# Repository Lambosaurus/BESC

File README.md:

# BESC

## Control-HW
This component is the ESC control board - that is, everything except the FET's.

Firmware for this is the [simon-k](https://github.com/sim-/tgy) `rb70a.hex`.

Based on this, the pinout will be:

| Signal         | Simon-k | Pin | 
| -------------- | ------- | --- |
| PWM_AL         | AnFET   | PD0 | 
| PWM_AH         | ApFET   | PD1 |
| PWM_BL         | BnFET   | PD3 |
| PWM_BH         | BpFET   | PD4 |
| PWM_CL         | CnFET   | PD7 |
| PWM_CH         | CpFET   | PD5 |
| RC_IN          | rcp_in  | PD2 |
| SENSE_A        | mux_a   | PC4 |
| SENSE_B        | mux_b   | PC3 |
| SENSE_C        | mux_c   | PC2 |
| SENSE_COM      | c_comp  | PD6 |
| VBATT_AIN      | mux_voltage | ADC7 |

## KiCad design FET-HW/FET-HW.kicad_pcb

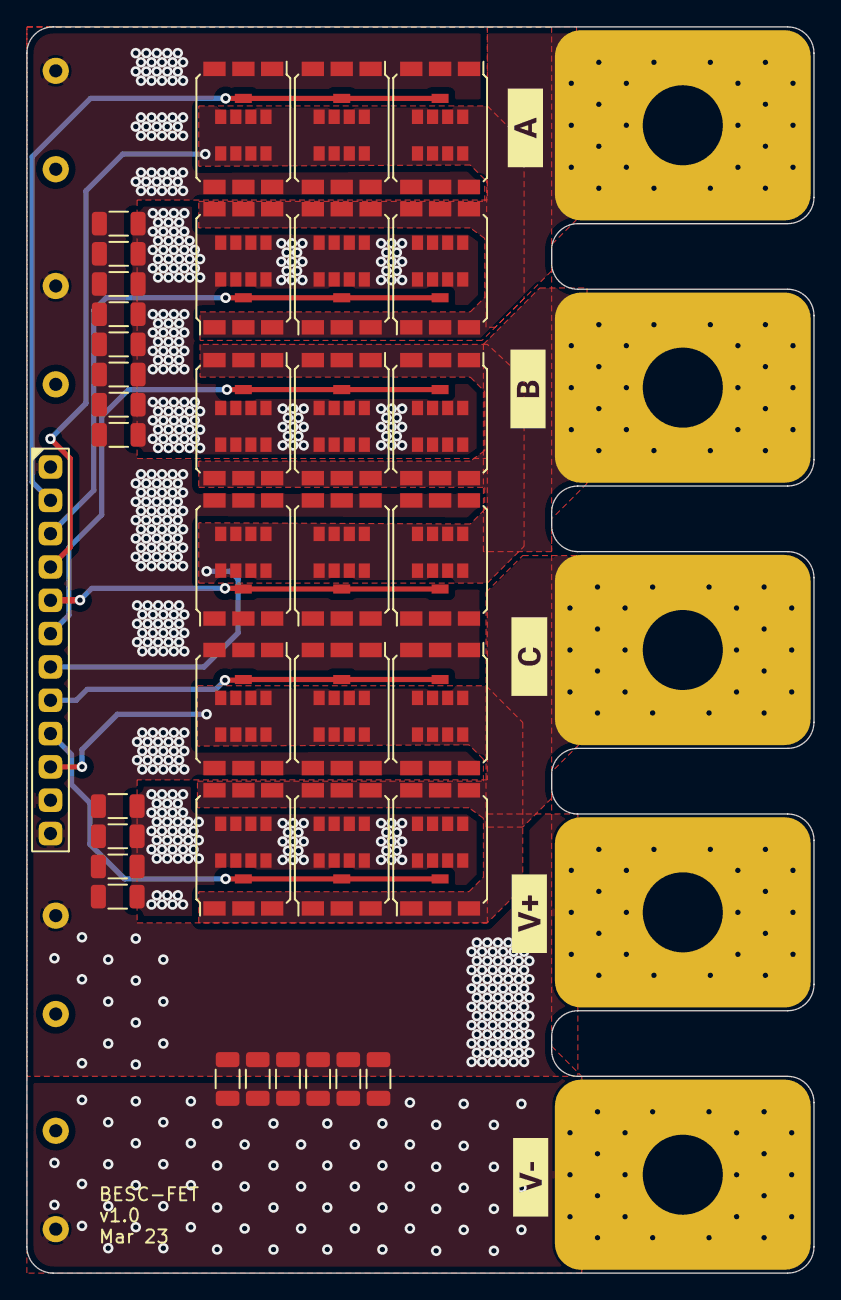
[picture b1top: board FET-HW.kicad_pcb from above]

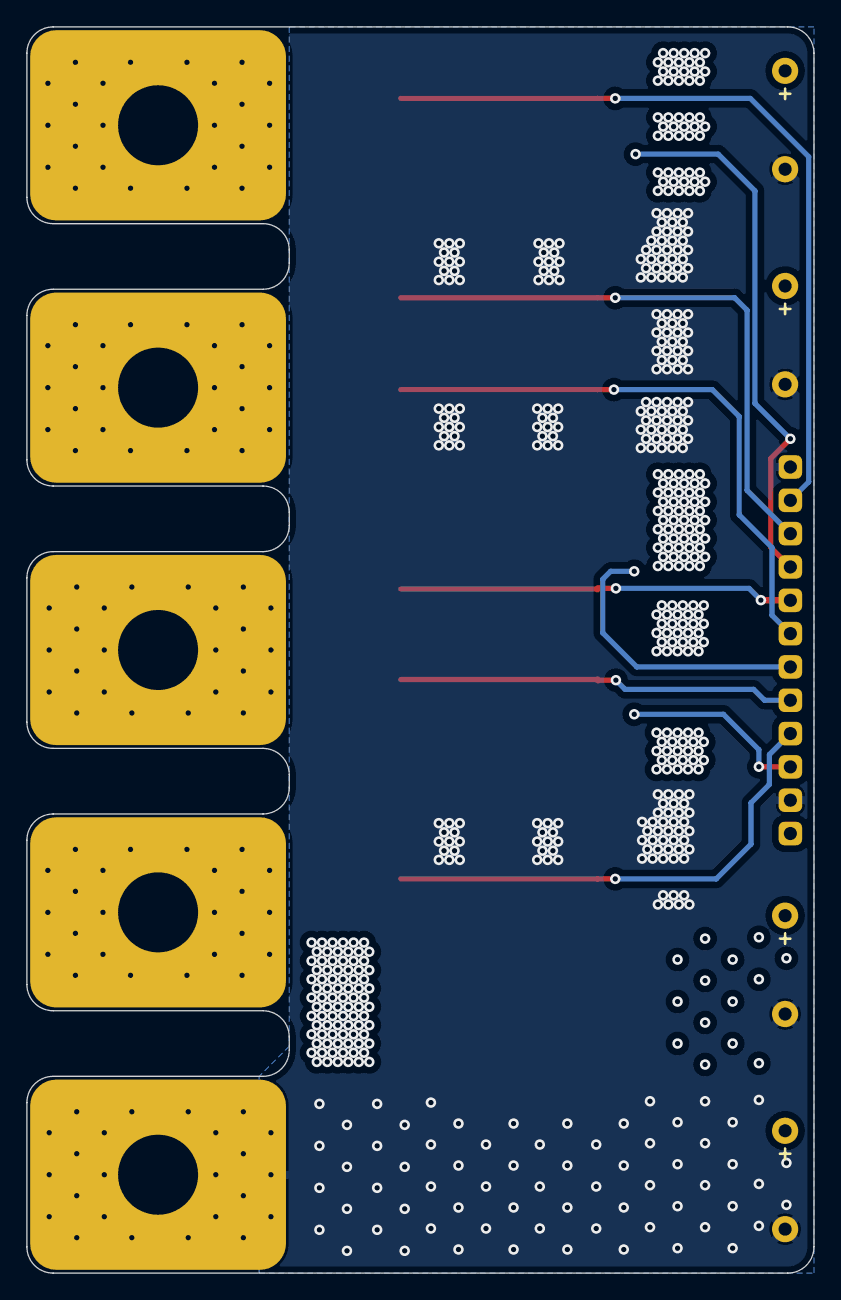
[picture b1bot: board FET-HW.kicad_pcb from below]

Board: 4 copper layers, 60.0 x 95.0 mm, 51 parts (4 on the bottom side), 11 nets.

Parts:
C1, C2, C3, C4, C5, C6, C7, C8, C9, C10, C11, C12, C13, C14, C15, C16, C17, C18: 4u7,100v; C_1206
C19, C20, C21, C22: 470u,100v; C_Radial_D16.0mm_H25.0mm_P7.50mm
J1: Pins_2.54_1x12; Pins-2.54-1x12
N1, N2, N3, N4, N5: Finger_15x20_M6
Q1, Q2, Q3, Q4, Q5, Q6, Q7, Q8, Q9, Q10, Q11, Q12, Q13, Q14, Q15, Q16, Q17, Q18: IRF7769L1TRPBF; IR_DirectFET_L8
kibuzzard-640441A5: G***; kibuzzard-640441A5
kibuzzard-640441AC: G***; kibuzzard-640441AC
kibuzzard-640441B5: G***; kibuzzard-640441B5
kibuzzard-6404419B: G***; kibuzzard-6404419B
kibuzzard-64044190: G***; kibuzzard-64044190

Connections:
+BATT: C1.1, C2.1, C3.1, C4.1, C5.1, C6.1, C7.1, C8.1, C9.1, C10.1, C11.1, C12.1, C13.1, C14.1, C15.1, C16.1, C17.1, C18.1, C19.1, C20.1, C21.1, C22.1, J1.12, N1.1, Q1.1 (D), Q3.1 (D), Q5.1 (D), Q7.1 (D), Q9.1 (D), Q11.1 (D), Q13.1 (D), Q15.1 (D), Q17.1 (D)
/GATE_AH: J1.2, Q7.2 (G), Q9.2 (G), Q11.2 (G)
/GATE_AL: J1.3, Q8.2 (G), Q10.2 (G), Q12.2 (G)
/GATE_BH: J1.5, Q1.2 (G), Q3.2 (G), Q5.2 (G)
/GATE_BL: J1.6, Q2.2 (G), Q4.2 (G), Q6.2 (G)
/GATE_CH: J1.8, Q13.2 (G), Q15.2 (G), Q17.2 (G)
/GATE_CL: J1.9, Q14.2 (G), Q16.2 (G), Q18.2 (G)
/PHASE_A: J1.4, N3.1, Q7.3 (S), Q8.1 (D), Q9.3 (S), Q10.1 (D), Q11.3 (S), Q12.1 (D)
/PHASE_B: J1.7, N4.1, Q1.3 (S), Q2.1 (D), Q3.3 (S), Q4.1 (D), Q5.3 (S), Q6.1 (D)
/PHASE_C: J1.10, N5.1, Q13.3 (S), Q14.1 (D), Q15.3 (S), Q16.1 (D), Q17.3 (S), Q18.1 (D)
GND: C1.2, C2.2, C3.2, C4.2, C5.2, C6.2, C7.2, C8.2, C9.2, C10.2, C11.2, C12.2, C13.2, C14.2, C15.2, C16.2, C17.2, C18.2, C19.2, C20.2, C21.2, C22.2, J1.1, J1.11, N2.1, Q2.3 (S), Q4.3 (S), Q6.3 (S), Q8.3 (S), Q10.3 (S), Q12.3 (S), Q14.3 (S), Q16.3 (S), Q18.3 (S)

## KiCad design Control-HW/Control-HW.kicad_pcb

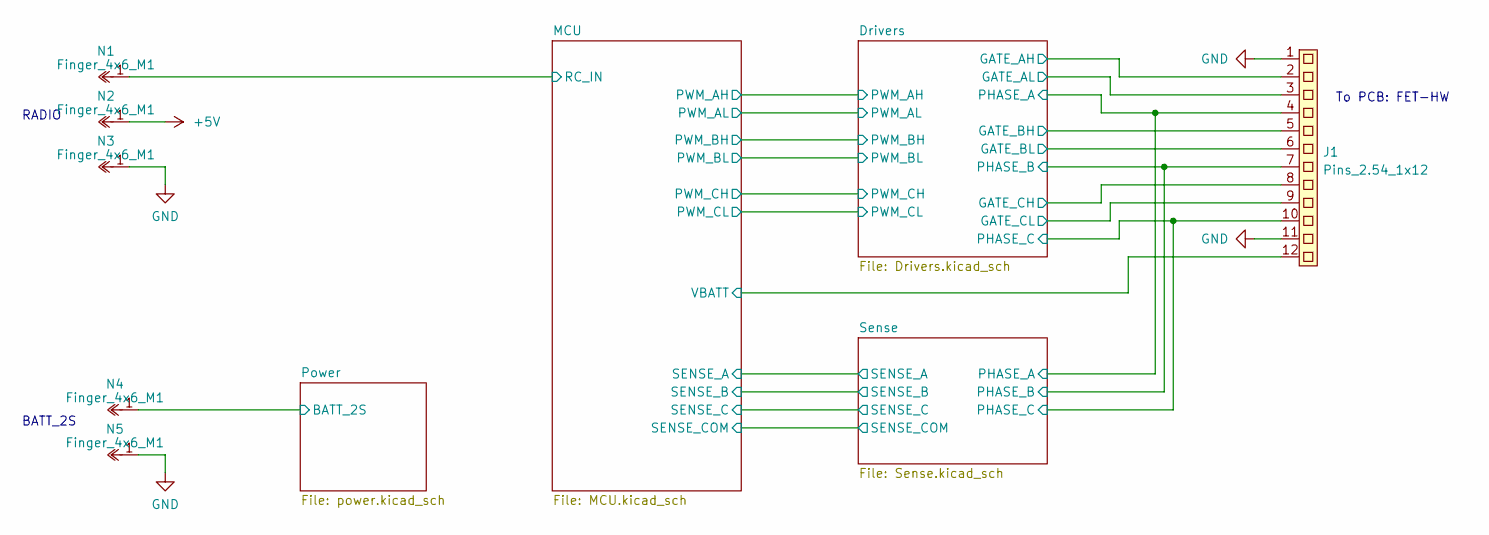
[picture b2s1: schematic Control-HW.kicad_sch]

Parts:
J1: Pins_2.54_1x12; Pins-2.54-1x12
N1, N2, N3, N4, N5: Finger_4x6_M1

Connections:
+5V: N2.1; also elsewhere on the board
/Drivers/GATE_AH: J1.2; also elsewhere on the board
/Drivers/GATE_AL: J1.3; also elsewhere on the board
/Drivers/GATE_BH: J1.5; also elsewhere on the board
/Drivers/GATE_BL: J1.6; also elsewhere on the board
/Drivers/GATE_CH: J1.8; also elsewhere on the board
/Drivers/GATE_CL: J1.9; also elsewhere on the board
/Drivers/PHASE_A: J1.4; also elsewhere on the board
/Drivers/PHASE_B: J1.7; also elsewhere on the board
/Drivers/PHASE_C: J1.10; also elsewhere on the board
/MCU/RC_IN: N1.1; also elsewhere on the board
/MCU/VBATT: J1.12; also elsewhere on the board
/Power/BATT_2S: N4.1; also elsewhere on the board
GND: J1.1, J1.11, N3.1, N5.1; also elsewhere on the board

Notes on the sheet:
BATT_2S
To PCB: FET-HW
RADIO

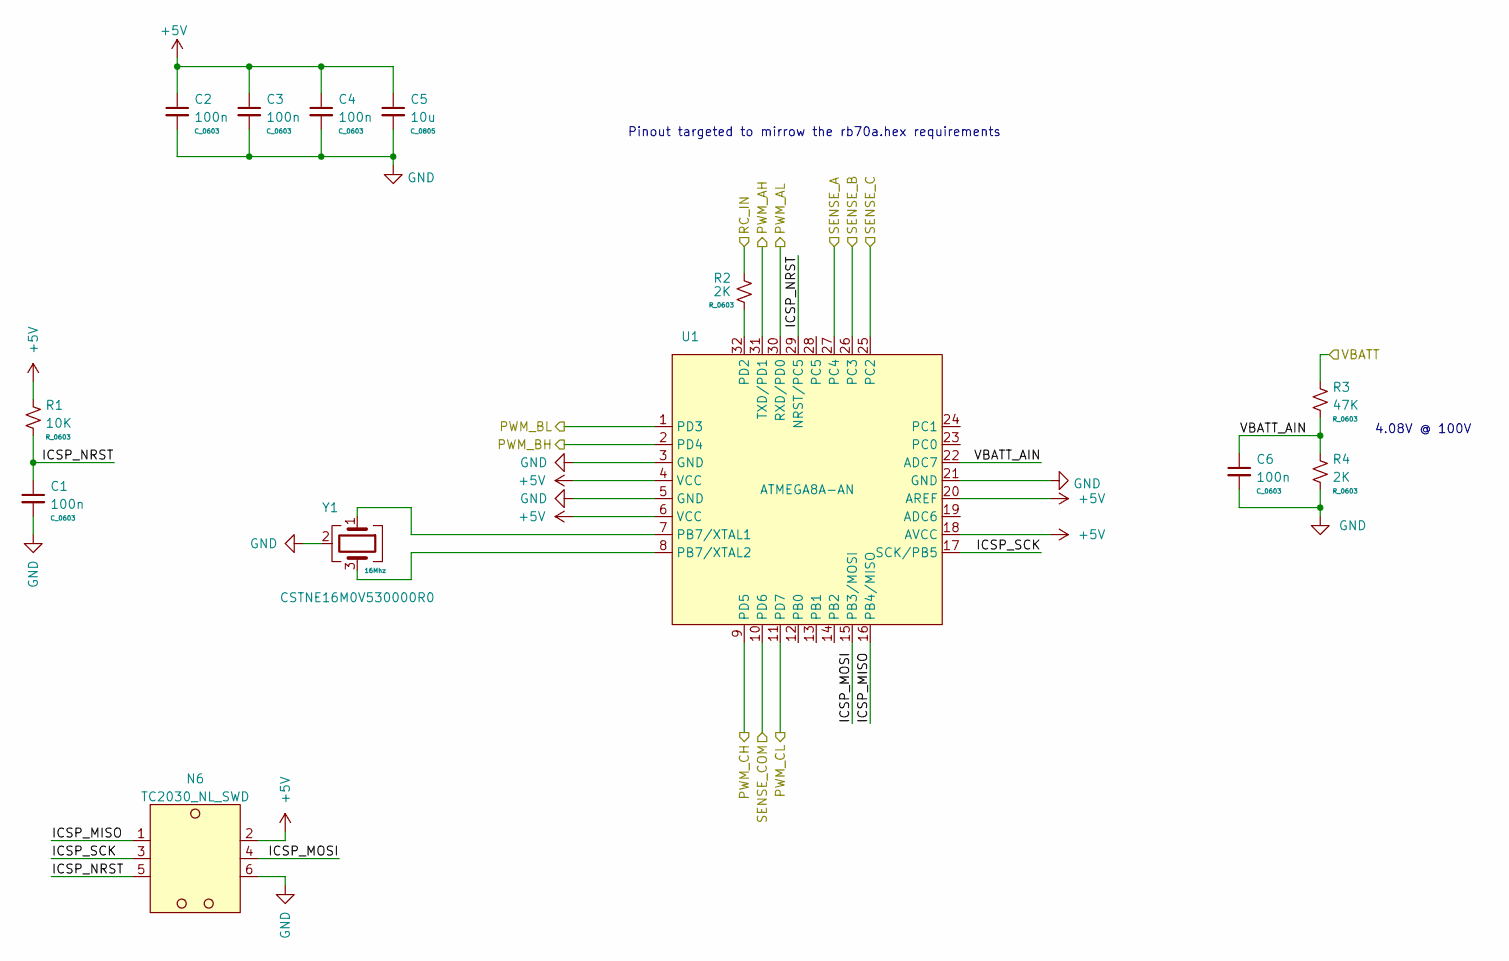
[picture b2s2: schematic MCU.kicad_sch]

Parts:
C1, C2, C3, C4, C6: 100n; C_0603
C5: 10u; C_0805
N6: TC2030_NL_SWD; TagConnect_TC2030_NL
R1: 10K; R_0603
R2, R4: 2K; R_0603
R3: 47K; R_0603
U1: ATMEGA8A-AN; LQFP32_08_7x7
Y1: CSTNE16M0V530000R0; Oscillator_SMD3_3.2x1.3

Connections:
+5V: C2.1, C3.1, C4.1, C5.1, N6.2, R1.1, U1.4 (VCC), U1.6 (VCC), U1.18 (AVCC), U1.20 (AREF); also elsewhere on the board
/Drivers/PWM_AH: U1.31 (TXD/PD1); also elsewhere on the board
/Drivers/PWM_AL: U1.30 (RXD/PD0); also elsewhere on the board
/Drivers/PWM_BH: U1.2 (PD4); also elsewhere on the board
/Drivers/PWM_BL: U1.1 (PD3); also elsewhere on the board
/Drivers/PWM_CH: U1.9 (PD5); also elsewhere on the board
/Drivers/PWM_CL: U1.11 (PD7); also elsewhere on the board
/MCU/ICSP_MISO: N6.1, U1.16 (PB4/MISO)
/MCU/ICSP_MOSI: N6.4, U1.15 (PB3/MOSI)
/MCU/ICSP_NRST: C1.1, N6.5, R1.2, U1.29 (NRST/PC5)
/MCU/ICSP_SCK: N6.3, U1.17 (SCK/PB5)
/MCU/RC_IN: R2.1; also elsewhere on the board
/MCU/SENSE_A: U1.27 (PC4); also elsewhere on the board
/MCU/SENSE_B: U1.26 (PC3); also elsewhere on the board
/MCU/SENSE_C: U1.25 (PC2); also elsewhere on the board
/MCU/SENSE_COM: U1.10 (PD6); also elsewhere on the board
/MCU/VBATT: R3.1; also elsewhere on the board
/MCU/VBATT_AIN: C6.1, R3.2, R4.1, U1.22 (ADC7)
GND: C1.2, C2.2, C3.2, C4.2, C5.2, C6.2, N6.6, R4.2, U1.3 (GND), U1.5 (GND), U1.21 (GND), Y1.2; also elsewhere on the board
unnamed: U1.7 (PB7/XTAL1), Y1.1
unnamed: U1.8 (PB7/XTAL2), Y1.3
unnamed: R2.2, U1.32 (PD2)

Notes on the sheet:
4.08V @ 100V
Pinout targeted to mirrow the rb70a.hex requirements

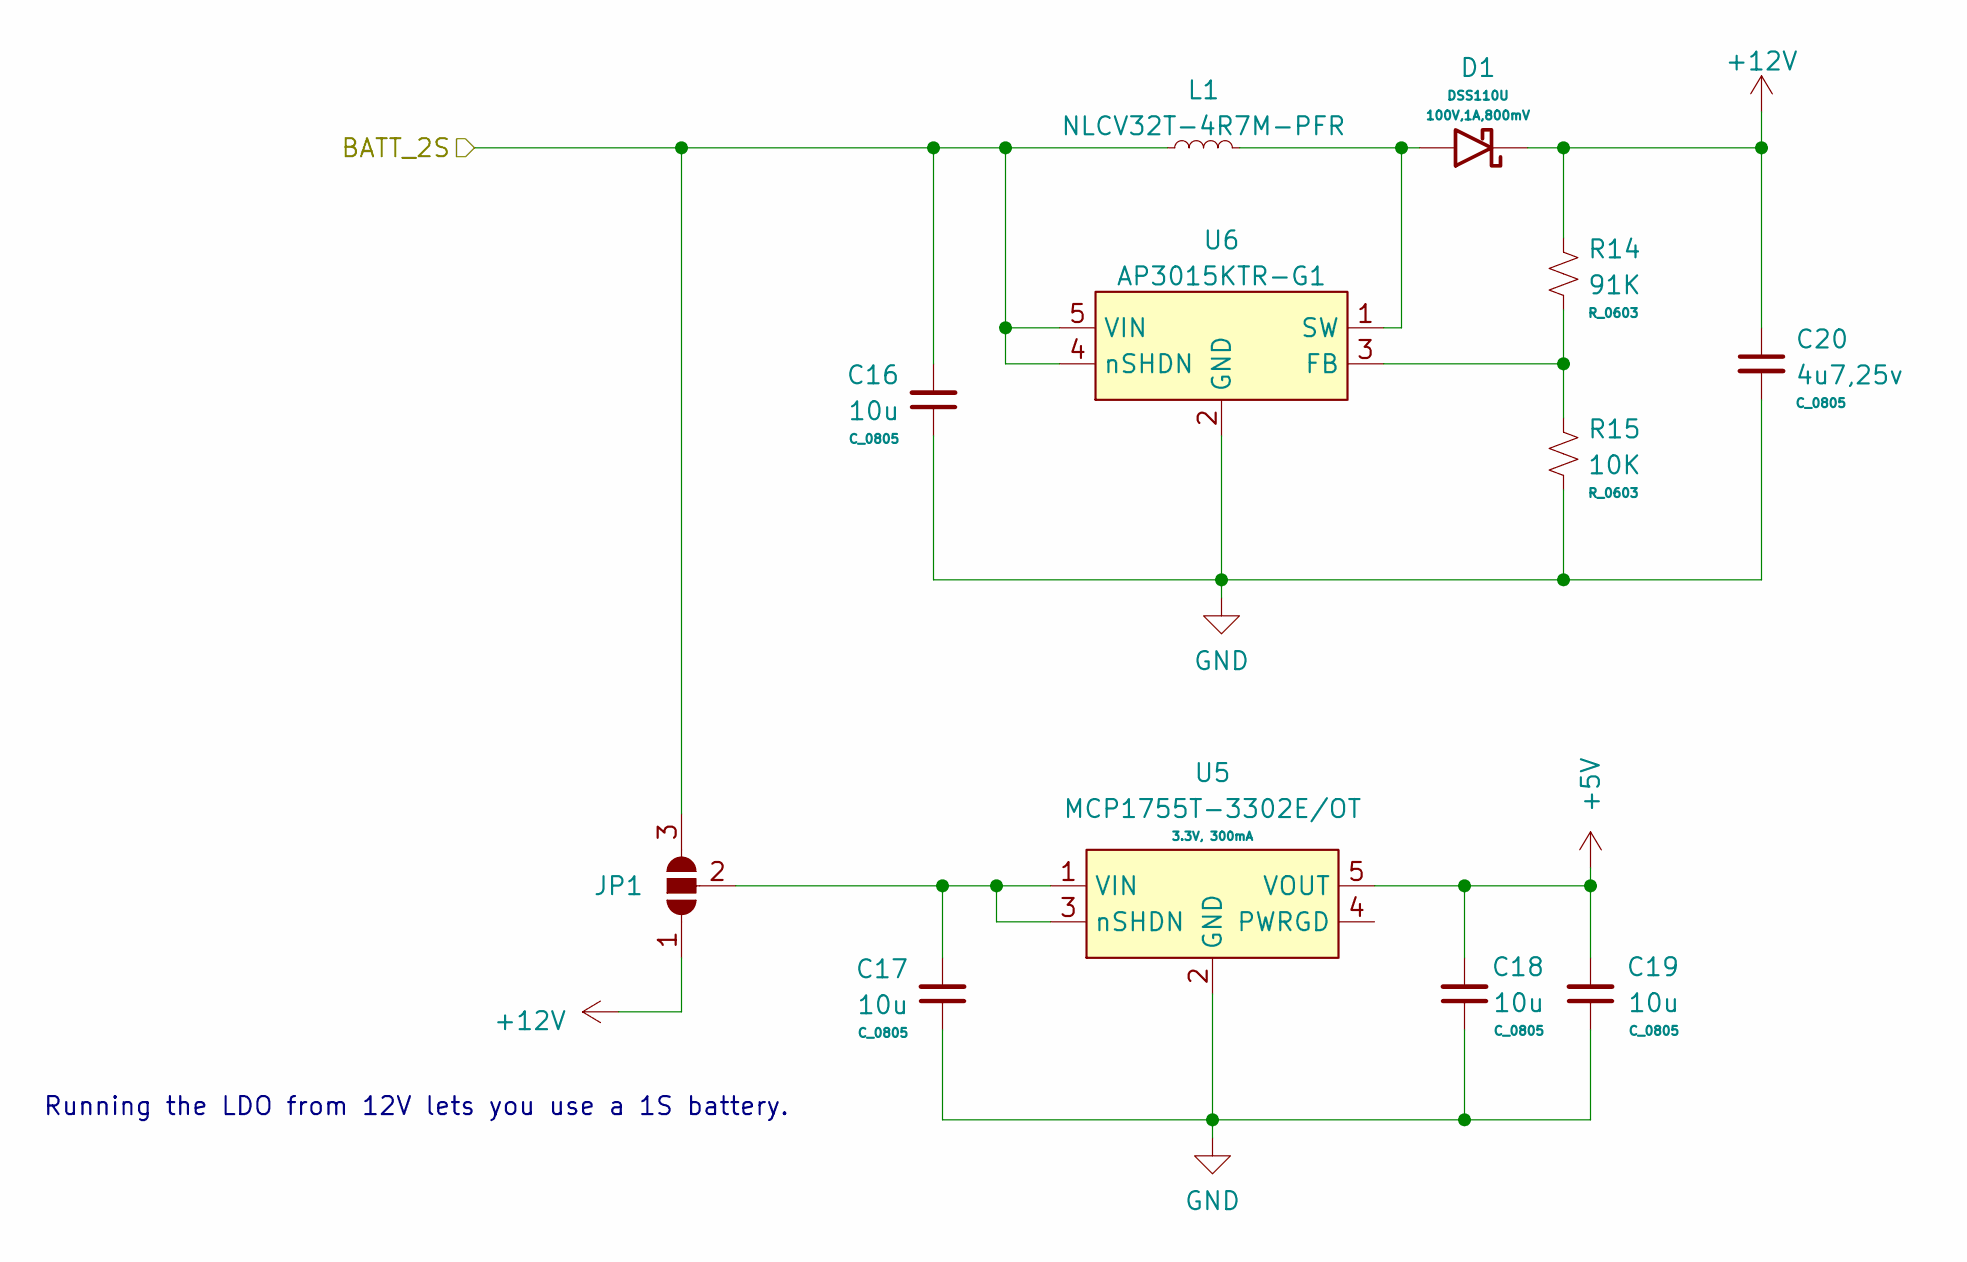
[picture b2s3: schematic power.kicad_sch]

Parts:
C16, C17, C18, C19: 10u; C_0805
C20: 4u7,25v; C_0805
D1: DSS110U; D_SOD_123
JP1: SolderJumper-3_P1.3mm_Open_RoundedPad1.0x1.5mm_NumberLabels
L1: NLCV32T-4R7M-PFR; L_1210
R14: 91K; R_0603
R15: 10K; R_0603
U5: MCP1755T-3302E/OT; SOT23_5
U6: AP3015KTR-G1; SOT23_5

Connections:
+5V: C18.2, C19.2, U5.5 (VOUT); also elsewhere on the board
+12V: C20.1, D1.1, JP1.1 (A), R14.1; also elsewhere on the board
/Power/BATT_2S: C16.2, JP1.3 (B), L1.1, U6.4 (nSHDN), U6.5 (VIN); also elsewhere on the board
GND: C16.1, C17.1, C18.1, C19.1, C20.2, R15.2, U5.2 (GND), U6.2 (GND); also elsewhere on the board
unnamed: C17.2, JP1.2 (C), U5.1 (VIN), U5.3 (nSHDN)
unnamed: R14.2, R15.1, U6.3 (FB)
unnamed: D1.2, L1.2, U6.1 (SW)

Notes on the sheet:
Running the LDO from 12V lets you use a 1S battery.

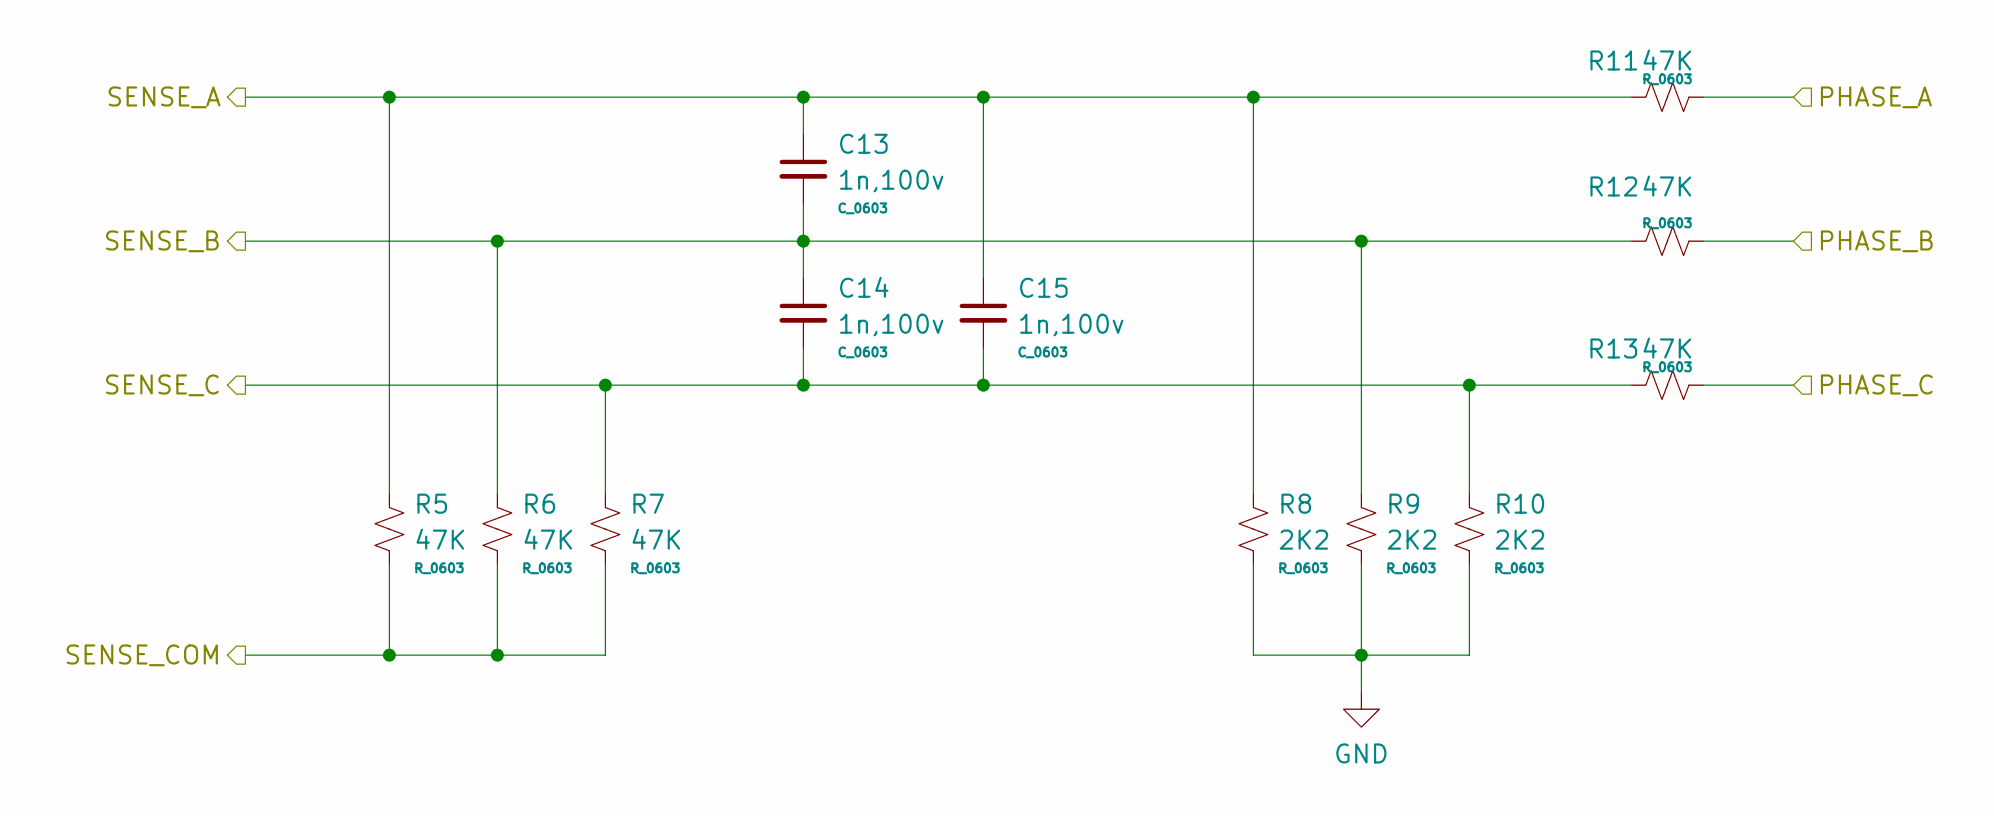
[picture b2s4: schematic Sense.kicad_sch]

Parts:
C13, C14, C15: 1n,100v; C_0603
R5, R6, R7, R11, R12, R13: 47K; R_0603
R8, R9, R10: 2K2; R_0603

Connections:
/Drivers/PHASE_A: R11.2; also elsewhere on the board
/Drivers/PHASE_B: R12.2; also elsewhere on the board
/Drivers/PHASE_C: R13.2; also elsewhere on the board
/MCU/SENSE_A: C13.1, C15.1, R5.1, R8.1, R11.1; also elsewhere on the board
/MCU/SENSE_B: C13.2, C14.1, R6.1, R9.1, R12.1; also elsewhere on the board
/MCU/SENSE_C: C14.2, C15.2, R7.1, R10.1, R13.1; also elsewhere on the board
/MCU/SENSE_COM: R5.2, R6.2, R7.2; also elsewhere on the board
GND: R8.2, R9.2, R10.2; also elsewhere on the board

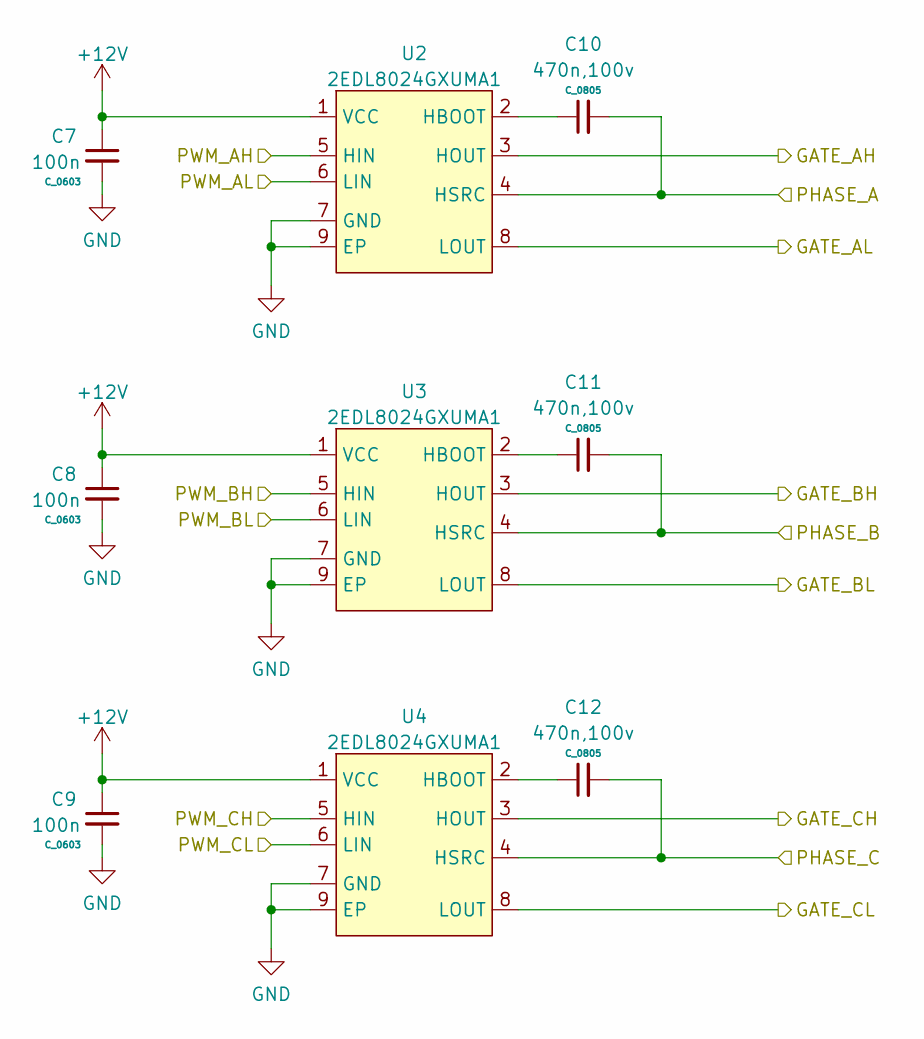
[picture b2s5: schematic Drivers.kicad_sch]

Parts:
C7, C8, C9: 100n; C_0603
C10, C11, C12: 470n,100v; C_0805
U2, U3, U4: 2EDL8024GXUMA1; DFN8_08_4x4_EP

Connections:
+12V: C7.1, C8.1, C9.1, U2.1 (VCC), U3.1 (VCC), U4.1 (VCC); also elsewhere on the board
/Drivers/GATE_AH: U2.3 (HOUT); also elsewhere on the board
/Drivers/GATE_AL: U2.8 (LOUT); also elsewhere on the board
/Drivers/GATE_BH: U3.3 (HOUT); also elsewhere on the board
/Drivers/GATE_BL: U3.8 (LOUT); also elsewhere on the board
/Drivers/GATE_CH: U4.3 (HOUT); also elsewhere on the board
/Drivers/GATE_CL: U4.8 (LOUT); also elsewhere on the board
/Drivers/PHASE_A: C10.2, U2.4 (HSRC); also elsewhere on the board
/Drivers/PHASE_B: C11.2, U3.4 (HSRC); also elsewhere on the board
/Drivers/PHASE_C: C12.2, U4.4 (HSRC); also elsewhere on the board
/Drivers/PWM_AH: U2.5 (HIN); also elsewhere on the board
/Drivers/PWM_AL: U2.6 (LIN); also elsewhere on the board
/Drivers/PWM_BH: U3.5 (HIN); also elsewhere on the board
/Drivers/PWM_BL: U3.6 (LIN); also elsewhere on the board
/Drivers/PWM_CH: U4.5 (HIN); also elsewhere on the board
/Drivers/PWM_CL: U4.6 (LIN); also elsewhere on the board
GND: C7.2, C8.2, C9.2, U2.7 (GND), U2.9 (EP), U3.7 (GND), U3.9 (EP), U4.7 (GND), U4.9 (EP); also elsewhere on the board
unnamed: C10.1, U2.2 (HBOOT)
unnamed: C11.1, U3.2 (HBOOT)
unnamed: C12.1, U4.2 (HBOOT)

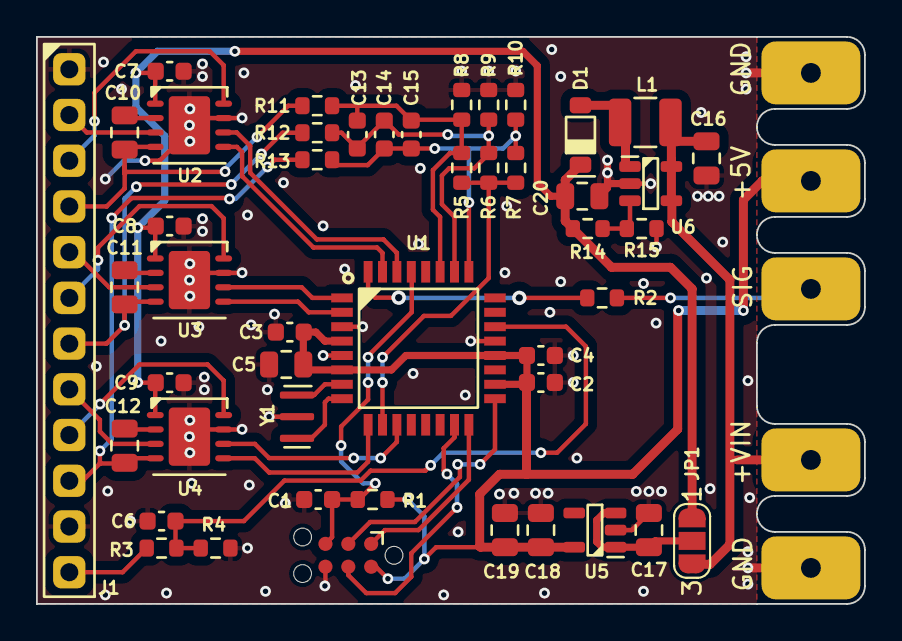
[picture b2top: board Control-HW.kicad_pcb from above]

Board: 2 copper layers, 46.0 x 31.5 mm, 52 parts (0 on the bottom side), 39 nets.

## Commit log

2023-02-17 Initial content
2023-02-17 Assign pinout for MCU
2023-03-04 First pass at control HW
2023-03-04 First revision
2023-03-04 Add FET-HW component
2023-03-04 Remember that I needed 3x FETS per leg
2023-03-05 First pass at FET PCB layout
2023-03-05 Add in some capacitance
2023-03-05 Put vias on fingers
2023-03-05 Add fp-info to gitignore
2023-03-07 Add TH capacitors
2023-03-18 Implemented control pcb
2023-03-18 Improve ground path a smidge
2023-03-18 Move some designators around
2023-03-19 Add output generation
2023-07-09 Add firmware build steps
